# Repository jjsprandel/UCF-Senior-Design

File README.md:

# 

Welcome to the **SCAN** repository! Below, you will find all the necessary information, from hardware design to software documentation.

---

## GitHub Workflows Status 🔧

Here are the current statuses of our GitHub workflows:

| Workflow Name            | Status                                  |
| ------------------------ | --------------------------------------- |
| **CI - Build**            |  |
| **Docker - Test Build**   |  |

- **CI - Build**: Ensures the project builds successfully.
- **CI - Tests**: Runs all unit and integration tests to ensure everything is working as expected.
- **Docker - Test Build**: Attempts Docker Build upon changes to the Dockerfile.

---

## Table of Contents 📚
- [💡 Overview](#overview)
- [🔧 Hardware Design](#hardware-design)
- [💻 Software](#software)
- [🔨 Build Instructions](#build-instructions)
- [📑 Documentation](#documentation)
- [⚙️ License](#license)

---

## 💡 Overview
 **SCAN** is a low-cost, IoT-driven kiosk system designed to provide real-time analytics based on check-in and check-out information. By integrating NFC-based authentication, real-time data processing, and a user-friendly interface, SCAN provides users with a near-effortless check-in experience and provides facilities with actionable insights for improving operations. SCAN is able to track attendance and provide detailed analytics on occupancy trends, peak usage hours, and visit durations. These insights are accessible to administrator and facility managers via SCAN’s web application, which can provide them with the necessary statistics to allocate resources efficiently, optimize staffing, and improve user experiences.

---

## 🔧 Hardware Design
<details>
  <summary><strong>📡 Schematic</strong></summary>

  Below is the schematic of the hardware design:

  **Key Features**:
  - Feature 1
  - Feature 2
  - Feature 3

  Additional hardware files can be found in the [hardware directory](hardware_design).

</details>

<details>
  <summary><strong>🔌 PCB Design</strong></summary>

  Here's the PCB design layout:

  **Important Notes**:
  - Note about the PCB.
  - Power considerations.
  - Any important design choices.

</details>

---

## 💻 Software
<details>
  <summary><strong>💾 Firmware Overview</strong></summary>

  The firmware is designed to work with the hardware for controlling the device. You can find the code [here](path/to/firmware).

  **Key Libraries Used**:
  - Library 1
  - Library 2

</details>

<details>
  <summary><strong>📦 Installation Guide</strong></summary>

  Follow these steps to install the firmware:
  
  1. Step 1
  2. Step 2
  3. Step 3

  Detailed instructions are available in the [installation guide](link_to_guide).

</details>

---

## 🔨 Build Instructions

<details>
  <summary><strong>🛠️ Build Setup</strong></summary>

  To build the project, follow these steps:

  1. Clone the repository:
     ```bash
     git clone https://github.com/jjsprandel/SCAN.git
     ```
  2. Reopen Visual Studio Code in Container:
  3. Compile the firmware:
     ```bash
     idf.py build
     ```
  4. Flash the firmware:
     ```bash
     idf.py --port 'rfc2217://host.docker.internal:4000?ign_set_control' flash
     ```

  **Tips**:
  - Ensure your system meets the requirements listed in the [build prerequisites](link_to_prerequisites).
  - If you encounter issues, check the [troubleshooting guide](link_to_troubleshooting).

</details>

---

## 📑 Documentation
<details>
  <summary><strong>📝 API Documentation</strong></summary>

  - **[API Reference](link_to_api_reference)**: Detailed API usage and function descriptions.
  - **[Hardware Docs](link_to_hardware_docs)**: Documentation on hardware design.

</details>

<details>
  <summary><strong>📚 Additional Resources</strong></summary>

  - **[Project Wiki](link_to_wiki)**: Explore the project wiki for more in-depth articles.
  - **[User Manual](link_to_user_manual)**: Comprehensive user guide for operation.

</details>

---

## 🔌 Dependencies

This project has the following dependencies that need to be installed:

### **Hardware Dependencies:**
- **KiCad Version**: 8.0.6 (required for schematic and PCB design)
  - Download from [KiCad official website](https://kicad.org/download/).
  
### **Software Dependencies:**
- **USB Drivers**: For proper communication with the hardware, ensure that the appropriate USB drivers are installed.
  - For Windows, you can download and install the **[CP210x USB to UART Bridge VCP drivers](https://www.silabs.com/developer-tools/usb-to-uart-bridge-vcp-drivers?tab=downloads)**.
  - For Linux, you should have the necessary drivers already built into the kernel, but check the [driver documentation](https://www.silabs.com/community/interface/usb-bridges) for troubleshooting.

- **Docker Desktop**: Required to run the ESP-IDF containerized environment.
  - Download from **[Docker Desktop website](https://www.docker.com/products/docker-desktop)**.
  - Follow the installation instructions for your operating system.
  
### **Development Tools:**
- **[Visual Studio Code](https://code.visualstudio.com/)**: Recommended IDE for editing the firmware code.

- **[Git](https://git-scm.com/)**: Version control system.

---

## ⚙️ License
SCAN © 2025 is licensed under Creative Commons Attribution-NonCommercial-NoDerivatives 4.0 International. To view a copy of this license, visit https://creativecommons.org/licenses/by-nc-nd/4.0/ or see the [LICENSE](LICENSE) file.

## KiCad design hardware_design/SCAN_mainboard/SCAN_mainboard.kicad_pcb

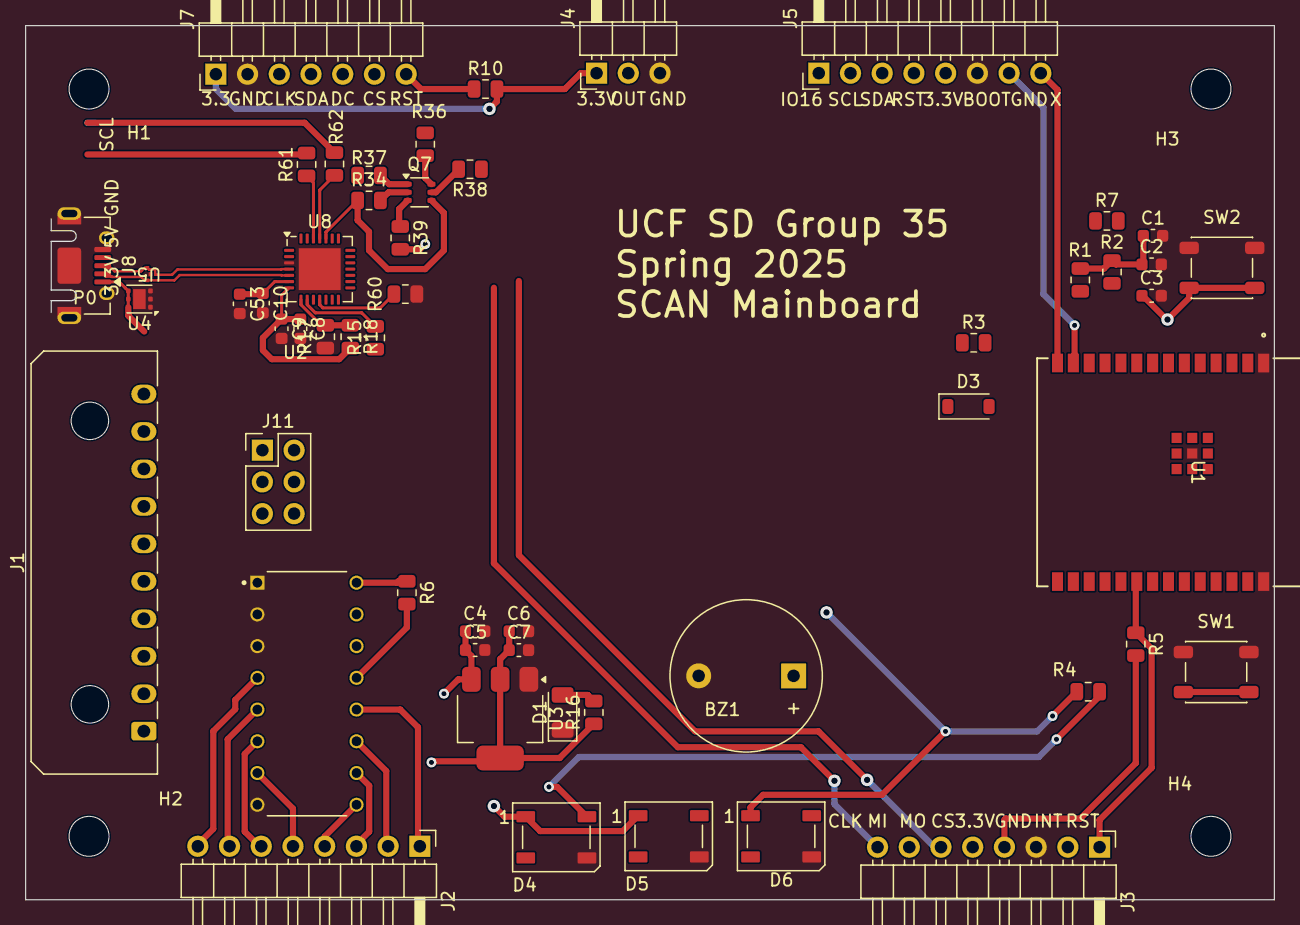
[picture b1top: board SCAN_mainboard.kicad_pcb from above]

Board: 2 copper layers, 100.0 x 70.0 mm, 58 parts (0 on the bottom side), 58 nets.

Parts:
BZ1: Buzzer; Buzzer_12x9.5RM7.6
C1: 10u; C_0603_1608Metric
C2: 0.1u; C_0603_1608Metric
C3: 1u; C_0603_1608Metric
C4, C6: 10uF; C_0603_1608Metric
C5, C7: 100nF; C_0603_1608Metric
C8, C53: .1u; C_0603_1608Metric
C9, C10: 4.7u; C_0603_1608Metric
D1: LED; LED_1206_3216Metric
D3: 1N4148W; D_SOD-123
D4: SUCCESS_LED; LED_WS2812B_PLCC4_5.0x5.0mm_P3.2mm
D5: FAILURE_LED; LED_WS2812B_PLCC4_5.0x5.0mm_P3.2mm
D6: ADMIN_LED; LED_WS2812B_PLCC4_5.0x5.0mm_P3.2mm
H1, H2, H3, H4: MountingHole_Pad; MountingHole_3.2mm_M3
J1: Conn_01x10; Molex_Micro-Fit_3.0_43650-1000_1x10_P3.00mm_Horizontal
J2: KEYPAD_CONN; PinHeader_1x08_P2.54mm_Horizontal
J3: PN532_CONN; PinHeader_1x08_P2.54mm_Horizontal
J4: PIR_CONN; PinHeader_1x03_P2.54mm_Horizontal
J5: DEBUG_BREAKOUT; PinHeader_1x08_P2.54mm_Horizontal
J7: TFT_CONN; PinHeader_1x07_P2.54mm_Horizontal
J8: USB_B_Micro; USB_Micro-AB_Molex_47590-0001
J11: PWR_MUX; PinHeader_2x03_P2.54mm_Vertical
Q7: BC847BDW1; SOT-363_SC-70-6
R1, R2: 2.2k; R_0805_2012Metric
R3, R4, R5, R6, R10, R34, R37: 10k; R_0805_2012Metric
R7: 3.3k; R_0805_2012Metric
R15, R16: 1k; R_0805_2012Metric
R17: 47.5k; R_0805_2012Metric
R18: 22.1k; R_0805_2012Metric
R36, R38, R39, R60, R61, R62: 0Ω; R_0805_2012Metric
SW1: RST_SWITCH; SW_SPST_PTS647_Sx38
SW2: SW_Push; SW_SPST_PTS647_Sx38
U1: ESP32-C6-WROOM-1-N8
U2: PCF8574; DIP794W45P254L1969H508Q16
U3: AMS1117-3.3; SOT-223-3_TabPin2
U4: TVS2200DRV; WSON-6-1EP_2x2mm_P0.65mm_EP1x1.6mm
U5: ESD122DMYR; DMY0003A
U8: CP2102N-A02-xQFN28; QFN-28-1EP_5x5mm_P0.5mm_EP3.35x3.35mm

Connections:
3.3V_LDO_OUT: C6.1, C7.1, J11.3, R16.1, U3.2 (VO)
3.3V_PWR_BRD: J1.2, J11.1
3.3V_SYS: C1.1, C2.1, J3.4, J4.1, J5.5, J7.1, J11.2, R1.1, R2.1, R3.1, R5.2, R6.1, R7.2, R10.2, U1.2 (3V3), U2.16 (VDD)
5V_PWR_BRD: J1.1, J11.4
5V_SYS: C4.1, C5.1, C8.1, C9.1, D4.1 (VDD), D5.1 (VDD), D6.1 (VDD), J11.5, R4.1, R18.2, U3.3 (VI), U8.7 (VREGIN)
/Auto Download/DTR: Q7.1 (E1), R37.1, U8.28 (~DTR)
/Auto Download/RTS: Q7.4 (E2), R34.1, U8.24 (~RTS)
/BOOT: J5.1, R36.2, SW1.2, U1.15 (GPIO9)
/BQ25798_INT: J1.6, U1.6 (GPIO6)
/BUZZER_PWM: BZ1.1 (+), U1.12 (GPIO11)
/CHIP_PU: C3.1, R3.2, R39.2, SW2.2, U1.3 (EN)
/GPIO12_BREAKOUT: J5.7, U1.13 (GPIO12)
/GPIO13_BREAKOUT: J5.8, U1.14 (GPIO13)
/I2C_SCL: J1.10, J5.2, R2.2, U1.8 (GPIO0), U2.14 (SCL)
/I2C_SDA: J1.9, J5.3, R1.2, U1.9 (GPIO1), U2.15 (SDA)
/KEYPAD_INT: R6.2, U1.26 (GPIO3), U2.13 (~INT)
/MICRO_USB_D+: J8.3 (D+), U5.2, U8.4 (D+)
/MICRO_USB_D-: J8.2 (D-), U5.3, U8.5 (D-)
/NFC_INT: J3.2, U1.17 (GPIO19)
/NFC_RST: J3.1, R5.1, U1.20 (GPIO22)
/P0: J2.8, U2.4 (P0)
/P1: J2.7, U2.5 (P1)
/P2: J2.6, U2.6 (P2)
/P3: J2.5, U2.7 (P3)
/P4: J2.4, U2.9 (P4)
/P5: J2.3, U2.10 (P5)
/P6: J2.2, U2.11 (P6)
/P7: J2.1, U2.12 (P7)
/PD_GPIO: J1.8, U1.4 (GPIO4)
/PD_INT: J1.7, U1.5 (GPIO5)
/PIR_OUT: J4.2, U1.21 (GPIO23)
/RGB_1: D3.2 (A), D4.4 (DIN), R4.2
/RGB_12: D4.2 (DOUT), D5.4 (DIN)
/RGB_23: D5.2 (DOUT), D6.4 (DIN)
/RGB_CTRL: D3.1 (K), J5.4, R7.1, U1.10 (GPIO8)
/SPI_CLK: J3.8, J7.3, U1.11 (GPIO10)
/SPI_CS: J3.5, U1.18 (GPIO20)
/SPI_MISO: J3.7, U1.27 (GPIO2)
/SPI_MOSI: J3.6, J7.4, U1.7 (GPIO7)
/TFT_CS: J7.6, U1.16 (GPIO18)
/TFT_DC: J7.5, U1.23 (GPIO15)
/TFT_RESET_N: J7.7, R10.1, U1.19 (GPIO21)
/UART_RXD: J1.4, R61.2, U1.24 (GPIO17)
/UART_TXD: J1.5, R62.2, U1.25 (GPIO16)
/USB-to-UART Bridge/RST: R15.2, U8.9 (~RST)
/USB-to-UART Bridge/RXD: R62.1, U8.25 (RXD)
/USB-to-UART Bridge/SUSPEND: R60.1, U8.11 (~SUSPEND)
/USB-to-UART Bridge/TXD: R61.1, U8.26 (TXD)
/USB-to-UART Bridge/VBUS_SNS: R17.2, R18.1, U8.8 (VBUS)
/USB-to-UART Bridge/VDD: C10.1, C53.1, R15.1, U8.6 (VDD)
AGND: BZ1.2 (-), C1.2, C2.2, C3.2, C4.2, C5.2, C6.2, C7.2, C8.2, C9.2, C10.2, C53.2, D1.1 (K), D4.3 (VSS), D5.3 (VSS), D6.3 (VSS), J3.3, J4.3, J5.6, J7.2, J8.5 (GND), J8.6 (Shield), R17.1, R60.2, SW1.1, SW2.1, U1.1 (GND), U1.28 (GND), U1.29 (GND), U2.1 (A0), U2.2 (A1), U2.3 (A2), U2.8 (VSS), U3.1 (GND), U4.1 (GND), U4.2 (GND), U4.3 (GND), U4.7 (GND), U5.1, U8.3 (GND), U8.29 (GND)
unnamed: D1.2 (A), R16.2
unnamed: Q7.2 (B1), R34.2
unnamed: Q7.6 (C1), R36.1
unnamed: Q7.5 (B2), R38.2
unnamed: Q7.3 (C2), R39.1
unnamed: R37.2, R38.1
VBUS: J8.1 (VBUS), J11.6, U4.4 (IN), U4.5 (IN), U4.6 (IN)

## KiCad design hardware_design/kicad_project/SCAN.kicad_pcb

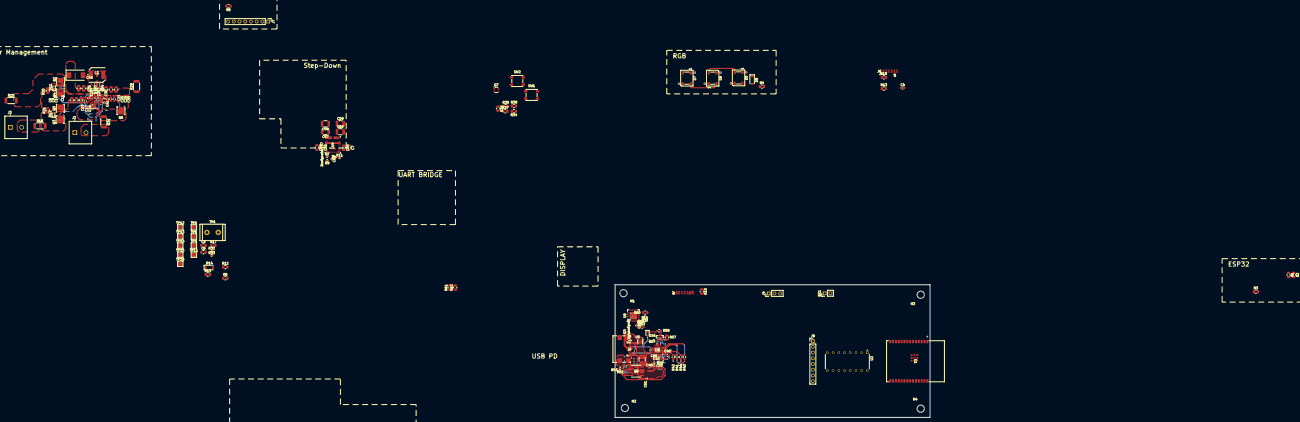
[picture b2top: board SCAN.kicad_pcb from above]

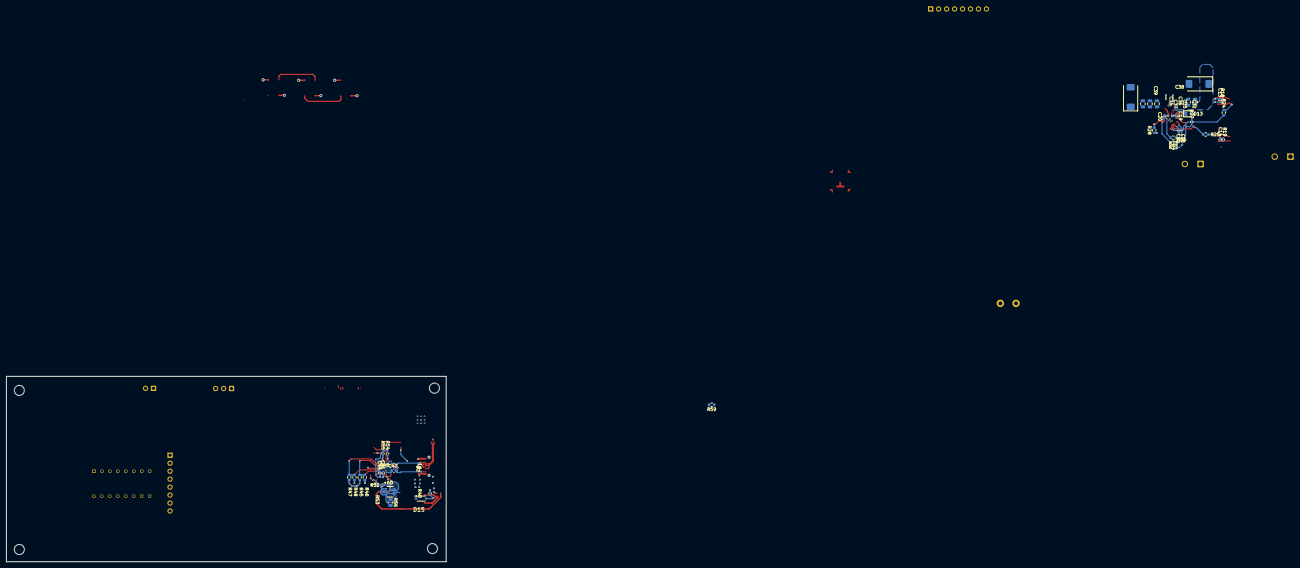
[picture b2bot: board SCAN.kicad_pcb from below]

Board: 4 copper layers, 140.0 x 59.0 mm, 177 parts (42 on the bottom side), 107 nets.

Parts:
BZ1: Buzzer; PinHeader_1x02_P2.54mm_Vertical
C4: 0.1u; C_0603_1608Metric
C5, C6: 1u; C_0805_2012Metric
C7, C8, C9, C10, C24, C25, C27, C28, C30, C31, C32, C34, C35, C36, C37, C54, C55, C56: 10u; C_0805_2012Metric
C11, C12, C15, C21, C22, C23, C44, C45, C53, C63: 0.1u; C_0402_1005Metric
C13, C14: 1nF; C_0402_1005Metric
C16, C17: 0.01u; C_0402_1005Metric
C18: 4.7u; C_0603_1608Metric
C19: 47n; C_0402_1005Metric
C20, C41: 47nF; C_0402_1005Metric
C26, C29, C33: 10u; C_0603_1608Metric
C38, C39, C40: 33u; CP_EIA-7343-31_Kemet-D
C43, C46: 1u; C_0603_1608Metric
C47, C48: 390p; C_0603_1608Metric
C49: 3.3u; C_1210_3225Metric
C50, C51, C61: 1u; C_0402_1005Metric
C57, C58, C59, C60: 22u; C_1210_3225Metric
C62: 1.0u; C_0603_1608Metric
C68: 100n; C_0402_1005Metric
D1, D2: ESD441; X2SON2_DPL_TEX
D5, D6, D7: WS2812B; LED_WS2812B_PLCC4_5.0x5.0mm_P3.2mm
D8, D14: 1N4148W; D_SOD-123
D11, D12: 12V; D_SOD-523
D13: LED; LED_0805_2012Metric
D15: NZH10C-115; SODFL3516X120N
D16: RED; LED_0603_1608Metric
H1, H2, H3, H4: MountingHole_Pad; MountingHole_3.2mm_M3
J1: USB_C_16P_Connector; USB4110-GF-A_GCT
J2: Batt_Connector; TE_282856-2
J3: PV_Panel_Connector; TE_282856-2
J4: PIR_CONNECTOR; PinHeader_1x03_P2.54mm_Vertical
J6, J8: Conn_01x12; 12-pin-0.7mm-FPC-Pad
J7: Conn_01x08; PinHeader_1x08_P2.54mm_Vertical
J9: Keypad; PinHeader_1x08_P2.54mm_Vertical
L1: 1.0u; SPM6530
Q2, Q3, Q4, Q5: CSD17581Q3A; VSON-8_3.3x3.3mm_P0.65mm_NexFET
Q6: CSD17575Q3; VSON-8_3.3x3.3mm_P0.65mm_NexFET
Q7: BC847BDW1; SOT-363_SC-70-6
Q8: IRF9358TRPBF; SO8_IRF9358TRPBF_INF
Q9: BSL308PE; PG-TSOP6-6-4_INF
Q10: NTR4503NT1G; SOT23_318-08_ONS
R1, R2: 2.2k; R_0805_2012Metric
R3, R4, R5, R6, R10, R10#2, R17, R34, R37, R60: 10k; R_0805_2012Metric
R7, R8, R18, R19: 100k; R_0402_1005Metric
R9: 19k; R_0402_1005Metric
R11: 32k; R_0402_1005Metric
R12: 15.4k; R_0805_2012Metric
R13, R13#2: 3.3k; R_0805_2012Metric
R14: 22.1k; R_0603_1608Metric
R15, R16: 0; R_2010_5025Metric
R20, R21, R36, R38, R39, R56, R61, R62: 0; R_0805_2012Metric
R22: 127k; R_0603_1608Metric
R23: 100k; R_0603_1608Metric
R24, R25: 294; R_0603_1608Metric
R26: 6.04k; R_0603_1608Metric
R27: 2.2k; R_0402_1005Metric
R28: 100; R_0603_1608Metric
R29, R31: 0.01; R_2010_5025Metric
R30: 47.5k; R_0603_1608Metric
R32: 5.24k; R_0402_1005Metric
R33: 30.1k; R_0402_1005Metric
R40, R52: 49.9k; R_0402_1005Metric
R41, R43: 5k; R_0603_1608Metric
R42, R48, R58: 1k; R_0603_1608Metric
R44: 2.4k; R_0603_1608Metric
R45, R46: 5.1k; R_0603_1608Metric
R47: DNP; R_0603_1608Metric
R49: 10k; R_0402_1005Metric
R50: 0; R_0402_1005Metric
R51, R53: 1k; R_0402_1005Metric
R54, R55: 2k; R_0402_1005Metric
R57: 100k; R_0805_2012Metric
R59: 4.7k; R_0603_1608Metric
SW1, SW2: SW_Push; SW_SPST_PTS647_Sx38
TH1: Thermistor_NTC; R_Radial_Power_L11.0mm_W7.0mm_P5.00mm
TP6, TP8, TP9, TP11, TP12, TP13, TP14, TP15, TP16: TestPoint; TestPoint_Pad_2.0x2.0mm
U1: ESP32-C6-WROOM-1-N8
U2: PCF8574; DIP794W45P254L1969H508Q16
U3: ESD122; DMY0003A
U4: BQ25798RQMR; IC_BQ25798RQMR
U5: TVS2200DRV; WSON-6-1EP_2x2mm_P0.65mm_EP1x1.6mm
U6: CYPD3177-24LQXQ; QFN50P400X400X60-25N-D
U8: CP2102N-A02-xQFN28; QFN-28-1EP_5x5mm_P0.5mm_EP3.35x3.35mm
U9: TPSM64406RCHR; RCH0028A-MFG

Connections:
1.8V_VCCD: C46.1, TP14.1, U6.24 (VCCD)
3.3V_SYS: C4.1, C59.1, C60.1, J4.1, J6.3 (LEDA), J6.4 (VDD), J7.5, J8.3 (LEDA), J8.4 (VDD), R1.1, R2.1, R3.1, R5.2, R6.1, R8.1, R10.2, R10#2.1, R13.2, R13#2.1, R17.1, U1.2 (3V3), U2.16 (VDD), U9.9 (COMP_VOSNS2), U9.18 (VOUT2), U9.19 (VOUT2)
3.3V_VDDD: C43.1, C44.1, C45.1, R41.1, R43.1, R45.1, R47.1, R54.1, R55.1, U6.23 (VDDD)
5V_SYS: C57.1, C58.1, C62.1, C63.1, D5.1 (VDD), D6.1 (VDD), D7.1 (VDD), R4.1, R7.1, R14.2, U8.7 (VREGIN), U9.3 (VOSNS1), U9.20 (VOUT1), U9.21 (VOUT1)
/Auto Download/DTR: Q7.1 (E1), R37.1, U8.28 (~DTR)
/Auto Download/RTS: Q7.4 (E2), R34.1, U8.24 (~RTS)
/BOOT: R36.2, SW1.2, U1.15 (GPIO9)
/BUZZER_PWM: BZ1.1 (-), U1.12 (GPIO11)
/CHGR_VOUT: R29.2, TP9.1
/CHIP_PU: R3.2, R39.2, SW2.2, U1.3 (EN)
/Display & RGB/RGB_1: D5.4 (DIN), D8.2 (A), R4.2
/Display & RGB/RGB_12: D5.2 (DOUT), D6.4 (DIN)
/Display & RGB/RGB_23: D6.2 (DOUT), D7.4 (DIN)
/Display & RGB/TFT_RESET_N: J6.11 (RST), R10#2.2
/I2C_SCL: R2.2, U1.8 (GPIO0), U2.14 (SCL), U4.14 (SCL), U6.13 (HPI_SCL)
/I2C_SDA: R1.2, U1.9 (GPIO1), U2.15 (SDA), U4.15 (SDA), U6.12 (HPI_SDA)
/KEYPAD_INT: R6.2, U1.26 (GPIO3), U2.13 (~INT)
/Keypad/P0: J9.1, U2.4 (P0)
/Keypad/P1: J9.2, U2.5 (P1)
/Keypad/P2: J9.3, U2.6 (P2)
/Keypad/P3: J9.4, U2.7 (P3)
/Keypad/P4: J9.5, U2.9 (P4)
/Keypad/P5: J9.6, U2.10 (P5)
/Keypad/P6: J9.7, U2.11 (P6)
/Keypad/P7: J9.8, U2.12 (P7)
/Logic Power/VCC: C61.1, U9.5 (VCC)
/NFC_INT: J7.7, U1.17 (GPIO19)
/NFC_RST: J7.8, R5.1, U1.20 (GPIO22)
/PD_GPIO: U1.4 (GPIO4), U6.8 (GPIO_1)
/PD_INT: R55.2, U1.5 (GPIO5), U6.7 (HPI_INT)
/PIR_OUT: J4.2, U1.21 (GPIO23)
/Power Management/ACDRV1: C16.1, R24.2, U4.11 (ACDRV1)
/Power Management/ACDRV2: C17.1, R25.2, U4.10 (ACDRV2)
/Power Management/BAT: C23.1, C26.1, C29.1, C33.1, Q6.1 (S), Q6.2 (S), Q6.3 (S), U4.22 (BAT), U4.23 (BAT)
/Power Management/BATP: C41.1, R28.1, U4.18 (BATP)
/Power Management/BAT_IN: J2.2, R31.2, TP11.1
/Power Management/BTST1: C19.1, U4.4 (BTST1)
/Power Management/BTST2: C20.1, U4.19 (BTST2)
/Power Management/ILIM_HIZ: R22.2, R23.1, U4.17 (ILIM_HIZ)
/Power Management/PMID: C7.1, C21.1, C24.1, C27.1, C31.1, C34.1, C36.1, C38.1, C40.1, C54.1, C55.1, C56.1, U4.29 (PMID), U9.2 (EN1), U9.10 (EN2), U9.14 (VIN2), U9.25 (VIN1)
/Power Management/PROG: R26.2, U4.20 (PROG)
/Power Management/PV_IN: C6.1, J3.2, R16.1
/Power Management/REGN: C18.1, R22.1, R27.1, R32.1, U4.5 (REGN)
/Power Management/SDRV: Q6.4 (G), U4.24 (SDRV)
/Power Management/STAT: D13.1 (K), U4.1 (STAT)
/Power Management/SW1: C19.2, L1.1, U4.28 (SW1)
/Power Management/SW2: C20.2, L1.2, U4.26 (SW2)
/Power Management/SYS: C22.1, C25.1, C28.1, C30.1, C32.1, C35.1, C37.1, C39.1, R29.1, TP6.1, U4.25 (SYS)
/Power Management/TS: R32.2, R33.1, TH1.1, U4.16 (TS)
/Power Management/VAC1: C12.1, Q2.5 (D), R15.2, R20.1, U4.9 (VAC1)
/Power Management/VAC2: C15.1, Q3.5 (D), R16.2, R21.1, U4.8 (VAC2)
/Power Management/VBUS: C8.1, C9.1, C10.1, C11.1, Q4.5 (D), Q5.5 (D), R20.2, R21.2, U4.2 (VBUS), U4.3 (VBUS)
/RGB_CTRL: D8.1 (K), R13#2.2, U1.10 (GPIO8)
/SAFE_PWR: Q9.4, R56.1, TP16.1
/SPI_CLK: J6.9 (SCL), J7.1, J8.9 (SCL), U1.11 (GPIO10)
/SPI_CS: J7.4, U1.18 (GPIO20)
/SPI_MISO: J7.2, U1.27 (GPIO2)
/SPI_MOSI: J6.10 (SDA), J7.3, J8.10 (SDA), U1.7 (GPIO7)
/TFT_CS: J6.8 (CS), J8.8 (CS), U1.16 (GPIO18)
/TFT_DC: J6.7 (DC), J8.7 (DC), U1.23 (GPIO15)
/TFT_RESET_N: J8.11 (RST), R10.1
/UART_RXD: R62.2, U1.14 (GPIO13)
/UART_TXD: R61.2, U1.13 (GPIO12)
/USB Power Delivery/FET2_SRC: Q9.2, Q9.5
/USB Power Delivery/FET_GATE: D15.2 (A), Q8.2, Q8.4, R40.2, R50.1
/USB Power Delivery/FET_SRC: D15.1 (K), Q8.1, Q8.3, R40.1
/USB Power Delivery/ISNK_CRS: R45.2, R46.1, U6.5 (ISNK_COARSE)
/USB Power Delivery/ISNK_FIN: R47.2, R48.1, U6.6 (ISNK_FINE)
/USB Power Delivery/PD_FAULT: Q10.1 (G), R57.1, U6.9 (FAULT)
/USB Power Delivery/PD_FLIP: R54.2, U6.10 (FLIP)
/USB Power Delivery/VBUS_MAX: R43.2, R44.1, TP13.1, U6.2 (VBUS_MAX)
/USB Power Delivery/VBUS_MIN: R41.2, R42.1, TP12.1, U6.1 (VBUS_MIN)
/USB-to-UART Bridge/RST: R59.2, U8.9 (~RST)
/USB-to-UART Bridge/RXD: R62.1, U8.25 (RXD)
/USB-to-UART Bridge/SUSPEND: R60.1, U8.11 (~SUSPEND)
/USB-to-UART Bridge/TXD: R61.1, U8.26 (TXD)
/USB-to-UART Bridge/VBUS_SNS: R14.1, R30.2, U8.8 (VBUS)
/USB-to-UART Bridge/VDD: C53.1, R59.1, U8.6 (VDD)
/USB_CC1: C48.1, D2.1, J1.A5 (CC1), U6.15 (CC1)
/USB_CC2: C47.1, D1.1, J1.B5 (CC2), U6.14 (CC2)
/USB_D+: J1.A6 (D+), J1.B6 (D+), U3.2, U8.4 (D+)
/USB_D-: J1.A7 (D-), J1.B7 (D-), U3.3, U8.5 (D-)
/USB_VBUS: C49.1, C50.1, C68.1, D16.2 (A), J1.A4-B9 (VBUS), J1.A9-B4 (VBUS), Q8.7, Q8.8, Q9.6, R49.1, R52.1, U5.4 (IN), U5.5 (IN), U5.6 (IN), U6.18 (VBUS_IN)
/VDC: C5.1, C51.1, Q8.5, Q8.6, R15.1, R56.2, TP15.1, U6.11 (VDC_OUT)
AGND: BZ1.2 (+), C4.2, C12.2, C15.2, C16.2, C17.2, C53.2, C57.2, C58.2, C59.2, C60.2, C61.2, C62.2, C63.2, D5.3 (VSS), D6.3 (VSS), D7.3 (VSS), J4.3, J6.1 (GND), J6.2 (LEDK), J6.5 (GND), J6.6 (GND), J6.12 (GND), J7.6, J8.1 (GND), J8.2 (LEDK), J8.5 (GND), J8.6 (GND), J8.12 (GND), R9.2, R11.2, R12.2, R17.2, R23.2, R26.1, R30.1, R33.2, R60.2, SW1.1, SW2.1, TH1.2, U1.1 (GND), U1.6 (GPIO6), U2.1 (A0), U2.2 (A1), U2.3 (A2), U2.8 (VSS), U4.13 (CE_N), U4.21 (INT_N), U8.3 (GND), U8.29 (GND), U9.11 (CONFIG)
unnamed: C50.2, C51.2, R49.2, R50.2, R51.1
unnamed: C13.1, D11.2 (A), Q2.1 (S), Q2.2 (S), Q2.3 (S), Q4.1 (S), Q4.2 (S), Q4.3 (S), R18.1
unnamed: C13.2, D11.1 (K), Q2.4 (G), Q4.4 (G), R18.2, R24.1
unnamed: C14.1, D12.2 (A), Q3.1 (S), Q3.2 (S), Q3.3 (S), Q5.1 (S), Q5.2 (S), Q5.3 (S), R19.1
unnamed: C14.2, D12.1 (K), Q3.4 (G), Q5.4 (G), R19.2, R25.1
unnamed: D13.2 (A), R27.2
unnamed: D14.2 (A), R13.1
unnamed: D16.1 (K), R58.1
unnamed: Q6.5 (D), R28.2, R31.1, TP8.1
unnamed: Q7.2 (B1), R34.2
unnamed: Q7.6 (C1), R36.1
unnamed: Q7.5 (B2), R38.2
unnamed: Q7.3 (C2), R39.1
unnamed: Q9.1, Q9.3, R52.2, R53.1
unnamed: Q10.3 (D), R58.2
unnamed: R37.2, R38.1
unnamed: R53.2, U6.4 (SAFE_PWR_EN)
unnamed: R51.2, U6.3 (VBUS_FET_EN)
unnamed: R7.2, R9.1, U9.4 (FB1)
unnamed: R12.1, U9.7 (RT)
unnamed: R8.2, R11.1, U9.8 (SS_FB2)
PGND: C5.2, C6.2, C7.2, C8.2, C9.2, C10.2, C11.2, C18.2, C21.2, C22.2, C23.2, C24.2, C25.2, C26.2, C27.2, C28.2, C29.2, C30.2, C31.2, C32.2, C33.2, C34.2, C35.2, C36.2, C37.2, C38.2, C39.2, C40.2, C41.2, C43.2, C44.2, C45.2, C46.2, C47.2, C48.2, C49.2, C54.2, C55.2, C56.2, C68.2, D1.2, D2.2, J1.15 (MH1), J1.16 (MH2), J1.17 (MH3), J1.18 (MH4), J1.A1-B12 (GND), J1.A12-B1 (GND), J2.1, J3.1, Q10.2 (S), R42.2, R44.2, R46.2, R48.2, R57.2, U3.1, U4.27 (GND), U5.1 (GND), U5.2 (GND), U5.3 (GND), U5.7 (GND), U6.19 (GND_1), U6.22 (GND_2), U6.25 (GND_3), U9.6 (AGND), U9.13 (PGND2), U9.26 (PGND1), U9.28 (EP)

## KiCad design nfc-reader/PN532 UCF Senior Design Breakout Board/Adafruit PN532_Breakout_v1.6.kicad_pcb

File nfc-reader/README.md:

# NFC Reader PlatformIO Project

## Overview
This project integrates NFC reading capabilities with a TFT display using various libraries. The main components include reading NFC tags and displaying information on a TFT screen.

## Dependencies

### Arduino Libraries
- **SPI.h**: SPI communication library.
- **PN532_SPI.h**: PN532 NFC controller library for SPI.
- **PN532.h**: PN532 NFC controller library.
- **NfcAdapter.h**: NFC adapter library.
- **Adafruit_GFX.h**: Adafruit GFX graphics core library.
- **Adafruit_GC9A01A.h**: Adafruit GC9A01A TFT display library.
- **Arduino.h**: Main Arduino library.

### Custom Libraries
- **tft_frames.h**: Custom header for TFT display frames.

### Submodules
This project uses several Git submodules for external libraries. Ensure you initialize and update the submodules after cloning the repository.

```sh
git submodule update --init --recursive

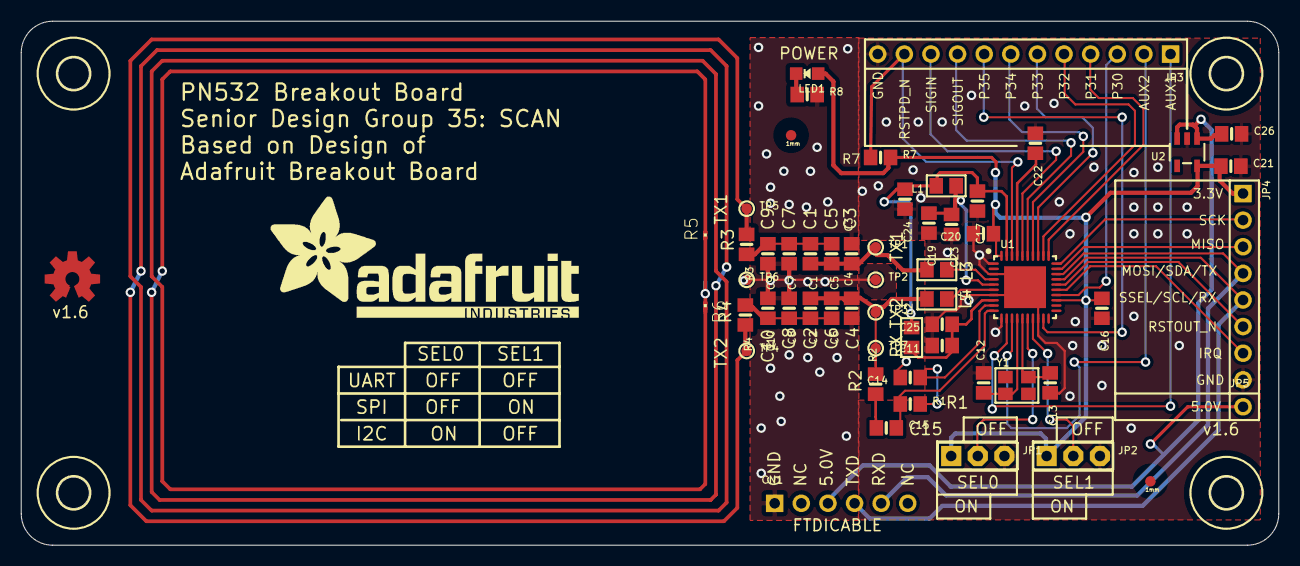
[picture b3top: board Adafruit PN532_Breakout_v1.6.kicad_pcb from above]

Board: 16 copper layers, 120.0 x 50.0 mm, 62 parts (0 on the bottom side), 40 nets.

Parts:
C1, C2: 22pF; 0805-NO
C3, C4: 220pF; 0805-NO
C5, C6, C9, C10: NC; 0805-NO
C7, C8: 100pF; 0805-NO
C11, C14, C16, C17, C20, C23, C24: 0.1µF; 0805-NO
C12, C13: 33pF; 0805-NO
C15: 1000pF; 0805-NO
C19, C21, C22, C25, C26: 10µF; 0805-NO
CN1: FTDI; 1X06_ROUND
FID1, FID2: FIDUCIAL1X2.5; FIDUCIAL-1X2.5
JP1: SEL0; JUMPER3
JP2: SEL1; JUMPER3
JP3: 1X12_ROUND
JP4: 1X08_ROUND
JP5: 1X01_ROUND
L1, L2: FERRITE; 0805
L3, L4: 560nH; 0805
LED1: GREEN; CHIPLED_0805_NOOUTLINE
R1: 1.0K; 0805-NO
R2: 1.69K; 0805-NO
R3, R4: 1.5; 0805-NO
R5, R6: NC; R0201
R7: 10K; 0805-NO
R8: TBD; 0805-NO
TP1: TX1_POST; TESTPOINT_ROUND_1MM
TP2, TP6: TGND; TESTPOINT_ROUND_1MM
TP3: TX2_POST; TESTPOINT_ROUND_1MM
TP4: TX2_PRE; TESTPOINT_ROUND_1MM
TP5: TX1_PRE; TESTPOINT_ROUND_1MM
TP7: RX; TESTPOINT_ROUND_1MM
U1: PN532; HVQFN40-6X6
U2: MIC5225-3.3V; SOT23-5
U$1: ADAFRUIT_TEXT_30MM
U$6, U$36, U$37, U$38: MOUNTINGHOLE_3.0
U$50: OSHWLOGO_TOP_0.2
Y1: 27.12MHz; CRYSTAL_3.2X2.5

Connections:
+5.0V: C26.1, CN1.3, JP5.1, U2.1, U2.3
AUX1: JP3.1, U1.12
AUX2: JP3.2, U1.13
GND: C3.2, C4.1, C7.2, C8.1, C9.2, C10.1, C11.2, C12.2, C13.2, C14.2, C16.2, C17.2, C19.2, C20.2, C21.2, C22.1, C23.2, C24.2, C25.2, C26.2, CN1.1, JP1.3, JP2.3, JP3.12, JP4.8, R5.2, R6.1, R8.2, TP2.P$1, TP6.P$1, U1.1, U1.3, U1.7, U1.11, U1.18, U1.TP, U2.2
IRQ: JP4.7, U1.25
MISO: JP4.3, U1.29
MOSI/SDA/TX: CN1.5, JP4.4, U1.28
unnamed: L3.2, U1.4
unnamed: L4.2, U1.6
unnamed: C1.2, C3.1, C5.2, L3.1, TP1.P$1
unnamed: R3.1, R6.2, TP5.P$1
unnamed: R4.2, R5.1, TP4.P$1
unnamed: LED1.C, R8.1
unnamed: C12.1, U1.14, Y1.1
unnamed: C13.1, U1.15, Y1.2
unnamed: C15.1, R2.1
unnamed: C14.1, R1.2, U1.9
unnamed: C15.2, R1.1, U1.10
unnamed: C2.1, C4.2, C6.1, L4.1, R2.2, TP3.P$1, TP7.P$1
unnamed: C11.1, C25.1, L2.1, U1.8
unnamed: C19.1, C23.1, L1.1, U1.5
unnamed: C22.2, U1.37
NSS/SCL/RX: CN1.4, JP4.5, U1.27
P30/UART_RX: JP3.3, U1.24
P31: JP3.4, U1.31
P32: JP3.5, U1.32
P33: JP3.6, U1.33
P34/SIC_CLK: JP3.7, U1.34
P35: JP3.8, U1.19
RSTOUT_N: JP4.6, U1.26
RSTPD_N: JP3.11, R7.1, U1.38
SCK: JP4.2, U1.30
SEL0: JP1.2, U1.16
SEL1: JP2.2, U1.17
SIGIN: JP3.10, U1.36
SIGOUT: JP3.9, U1.35
TX1_ANTENNA: C1.1, C5.1, C7.1, C9.1, R3.2
TX2_ANTENNA: C2.2, C6.2, C8.2, C10.2, R4.1
VCC: C17.1, C24.1, L1.2, L2.2, U1.39
VDD: C16.1, C20.1, C21.1, JP1.1, JP2.1, JP4.1, LED1.A, R7.2, U1.23, U1.40, U2.5

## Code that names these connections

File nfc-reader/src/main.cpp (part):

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#define API_KEY "AIzaSyBoHGBRg7e_thFtbURSlMAmlvfFNAQ8X1M"
#define DATABASE_URL "https://scan-9ee0b-default-rtdb.firebaseio.com/"

#define SPI_CLK 18
#define SPI_MOSI 23
#define SPI_MISO 19
#define SPI_CS_NFC 5

const int pirPin = 4;  // Use the GPIO pin where the AM312 OUT pin is connected
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// Pinout when using Seed Round Display for XIAO in combination with
// Seeed XIAO RP2040. Other (non-RP2040) XIAO boards, any Adafruit Qt Py
// boards, and other GC9A01A display breakouts will require different pins.
#define TFT_CS D1 // Chip select
#define TFT_DC D3 // Data/command
#define TFT_BL D6 // Backlight control

#else // ALL OTHER BOARDS - EDIT AS NEEDED
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// Other RP2040-based boards might not have "D" pin defines as shown above
// and will use GPIO bit numbers. On non-RP2040 boards, you can usually use
// pin numbers silkscreened on the board.
#define TFT_DC  32
#define TFT_CS 33
// If display breakout has a backlight control pin, that can be defined here
// as TFT_BL. On some breakouts it's not needed, backlight is always on.

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
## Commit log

2024-10-27 Initial Embedded Directory Structure
    Initial upload for embedded software directory structure. Includes code relating to PIR sensor interfacing. Further commits should be made to feature branches.
2024-10-27 Deleting directory to rename subfolder
2024-10-27 Initial embedded application structure
    Includes PIR integration as well. All further commits should be made using feature branches
2024-10-27 fix ino
2024-10-28 Converted project to Platforim IO Project and added WOWKI simulator
2024-10-29 Change from Arduino IDE to PlatformIO
2024-11-03 Functioning test for sending and receiving data to/from firebase realtimedb
2024-11-03 Reformatted database tester code to use custom library
2024-11-03 Updated driver src file to use data and time for logging events
2024-11-04 created nfc-reader project
2024-11-05 created schematic with all major components
2024-11-06 Docker setup for CI/CD. Working components: 1. idf.py build
2024-11-07 Adding GitHub Workflow. First test.
2024-11-07 prototype of nfc reader program
2024-11-10 added format, read, and write functionality for the NFC application
2024-11-10 setup graphics drivers and basic kiosk authentication messages
2024-11-11 Added remote serial server for flashing esp32 from Docker container
2024-11-12 added support for interacting with database api via keyboard input
2024-11-12 Created getUserInfo function for pulling user check-in status and passkey from database
2024-11-12 Factored back in PIR Sensor stuff
2024-11-12 first attempt at integrating nfc-reader with display. Issues with shared SPI bus still need to be resolvec
2024-11-12 Latest commit with FSM and working environment
2024-11-12 minor changes to schematic
2024-11-12 small change in python script
2024-11-12 small change 2
2024-11-12 change 3
2024-11-13 Added ESP32-C6 to schematic and organized schematic into inputs, outputs, and power circuit
2024-11-13 added readme and git submodules
2024-11-14 idek
2024-11-14 started power circuitry
2024-11-14 merged local changes with incoming remote for the kicad schematic
2024-11-15 fully integrated NFC reader and TFT display on shared SPI bus. Read for integration with PIR sensor and database for demo purposes
2024-11-16 reorganized structure and deleted empty projects
2024-11-16 idek dude
2024-11-16 created schematic for NFC module
2024-11-16 reorganization
2024-11-17 integrated nfc reader and user database
2024-11-17 usb pd work on power schematic sheet
2024-11-17 tested keypad functionality and began integration with IO expander
2024-11-17 updated NFC module schematic
2024-11-17 power work
2024-11-18 minor changes for demo video
2024-11-18 added NFC and PIR schematics to the document
2024-11-18 more power work
2024-11-18 minor changes to schematic for IO bus expander
2024-11-19 more power
2024-11-19 usb pd schematic
2024-11-21 minor modifications for the demo video
2024-11-21 power management schematic
2024-11-21 connected peripherals in schematic
2024-11-21 final schematic draft
2024-11-25 everything
2024-11-25 tested components for report and created schematic for PN532 circuit
2024-11-25 updated full systems schematic with peripheral connections
2024-11-25 added interrupt pin to keypad bus
2024-11-25 First full schematic
2024-11-26 Added power switch
2024-11-26 Added test points
2024-11-26 final edits befor report submission
2024-11-29 added entrypoint file edited CMake file to change main to src folder removed temporary folders for source code need to fix python script to build from local dockerfile instead of dockerhub
2024-11-30 changed python script to point to jjsprandel docker image
2024-11-30 removed automatic task kill on port 4000 added wifi component, no functionality yet fixed main and cmakelists file
2024-12-03 wifi functionality added in source code github actions updated to test docker image builds and upload esp32 build output
2024-12-03 Workflow for new code releases and triggers
2024-12-03 fixing workflow files
2024-12-03 trying again
2024-12-03 test
2024-12-03 test again
2024-12-03 test again again
2024-12-03 trying again again again
2024-12-03 again
2024-12-03 again 2
2024-12-04 trying
2024-12-04 release major
2024-12-04 major release
2024-12-12 commit from within remote window of vscode
2025-01-04 changes not pushed
2025-01-06 moved kicad schematic to main branch
2025-01-06 added readme - still needs to be edited
2025-01-08 Started working dashboard
2025-01-08 network security for rfc 2217 server and more
2025-01-08 branch protection
2025-01-09 test commit
2025-01-09 added build workflow
2025-01-09 small change
2025-01-09 minor release
2025-01-09 trying again again
2025-01-09 testing still
2025-01-09 testing again
2025-01-09 last commit
2025-01-09 last last commit
2025-01-09 last last last
2025-01-09 wrong GitHub Action version
2025-01-09 please work
2025-01-09 small changes
2025-01-10 implemented keypad password entering feature using IO expander
2025-01-11 squash to rebase
    branch protection
    test commit
2025-01-11 added build workflow
    trying again
    small change
    minor release
    trying again
    minor release
    trying again again
2025-01-11 Squash PR (#61)
2025-01-11 squash and rebase (#60)
    * branch protection
    * test commit
    * added build workflow
    * trying again
    * small change
    * minor release
2025-01-11 rebase to dev
    parent 509cb533aae13797c2d180f3da14037c77512b1f
    author Jonah Sprandel <116921084+jjsprandel@users.noreply.github.com> 1736574092 -0500
    committer Jonah Sprandel <jjsprandel@gmail.com> 1736576494 -0500
    rebase to dev branch
    parent 509cb533aae13797c2d180f3da14037c77512b1f
    author Jonah Sprandel <116921084+jjsprandel@users.noreply.github.com> 1736574092 -0500
2025-01-11 Rebase to dev
2025-01-13 updating sdkconfig to use sdkconfig.defaults and started OTA code
2025-01-15 website v1
2025-01-15 partition table setup
2025-01-15 Added sdkconfig to gitignore
2025-01-15 created feature branch for display driver
2025-01-16 working MBEDTLS handshake with github.com URL for OTA updates
2025-01-17 setup nfc reader code and working on extracting data from blocks
2025-01-18 http connectin not working
2025-01-19 Working OTA updates - LED will change from blinking blue to blinking green after OTA update
2025-01-19 added tasks for nfc_init, format, read, and write. Authentication errors
2025-01-20 changed circuit for TFT display and added datasheets to directory
2025-01-22 3 pages mostly working
2025-01-22 fixed block authentication errors and created NDEF component (WIP)
2025-01-24 created and completed source files for NDEF component
2025-01-24 finished power management footprints and started layout
2025-01-24 footprint assignments and fixed PN532 breakout
2025-01-24 latest
2025-01-27 created NDEF component, added keypad component to branch, and created test directory. Unit test framework WIP
2025-01-28 Login and signup pages layout, navbar issue persists
2025-01-28 using href in navbar causing page reload and clearing stored auth status
2025-01-28 merged card_reader and NDEF libraries and integrated keypad and PN532 tasks in app_main. NDEF message formatting WIP
2025-01-29 development of NDEF component
2025-01-30 firebase code and PCB layout
2025-01-31 reconfigured card reader to read/write to NTAG213 cards and wrote freeRTOS tasks to write IDs and read IDs in NDEF
2025-02-01 Added CRUD operations to use management page
2025-02-01 Added cloud function to update occupancy based on activity log updates
2025-02-01 NFC tasks defined in NDEF component are ready for integration. Started initial state control logic in main.c (WIP)
2025-02-01 Updated dashbaord to use firebase cloud functions backend to compute occupancy and average stay statistics (average stay still needs cloud funciton update)
2025-02-02 updated cloud function to update user checkin status and other fields upon activity log event
2025-02-02 fixed cloud functions so that average stay duration is now calculated properly
2025-02-02 added backend function for updating occupancy histogram every hour
2025-02-02 Added new firebase cloud function to update histogram data with number of checked in users every hour. Added dropdowns for location and day of the week to histogram card on dashboard page. Website no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
2025-02-03 setup LVGL example for creating display UI in the
2025-02-03 LVGL setup with basic display states. Created component for misc src files including pir and buzzer. Began development of kiosk state machine
2025-02-03 working (albeit buggy) kiosk state machine with PIR sensor, keypad, NFC reader, and mock database transmission. Display integration WIP
2025-02-03 hardware design work
2025-02-06 latest PCB
2025-02-07 missing firebase cert, not sure if correct one
2025-02-07 firebase working
2025-02-10 created new mainboard PCB (original PCB minus the power control circuitry)
2025-02-10 changed pin headers from vertical to horizontal and added connector for power inputs
2025-02-10 rerouting power pcb and fixed compile errors with Dre working on firebase firmware
2025-02-12 added halting with event groups for proximity sensor, NFC, and keypad tasks. Integrated display into state machine and rearranged states.
2025-02-12 oops
2025-02-12 Added missing breakout connections to power PCB
2025-02-13 more hardware fixes
2025-02-13 more pcb edits
2025-02-13 Updated schematic with CP2102N changes and other changes discussed in our 2/12/2025 meeting
2025-02-13 Updated schematic errors as per Dre's instructions
2025-02-14 swapped uart pins and added headers for power input muxing
2025-02-14 reorganize
2025-02-14 actually saved this time
2025-02-14 Layout progress for Dre changes
2025-02-14 Changed external connector to power PCB and reworked layout
